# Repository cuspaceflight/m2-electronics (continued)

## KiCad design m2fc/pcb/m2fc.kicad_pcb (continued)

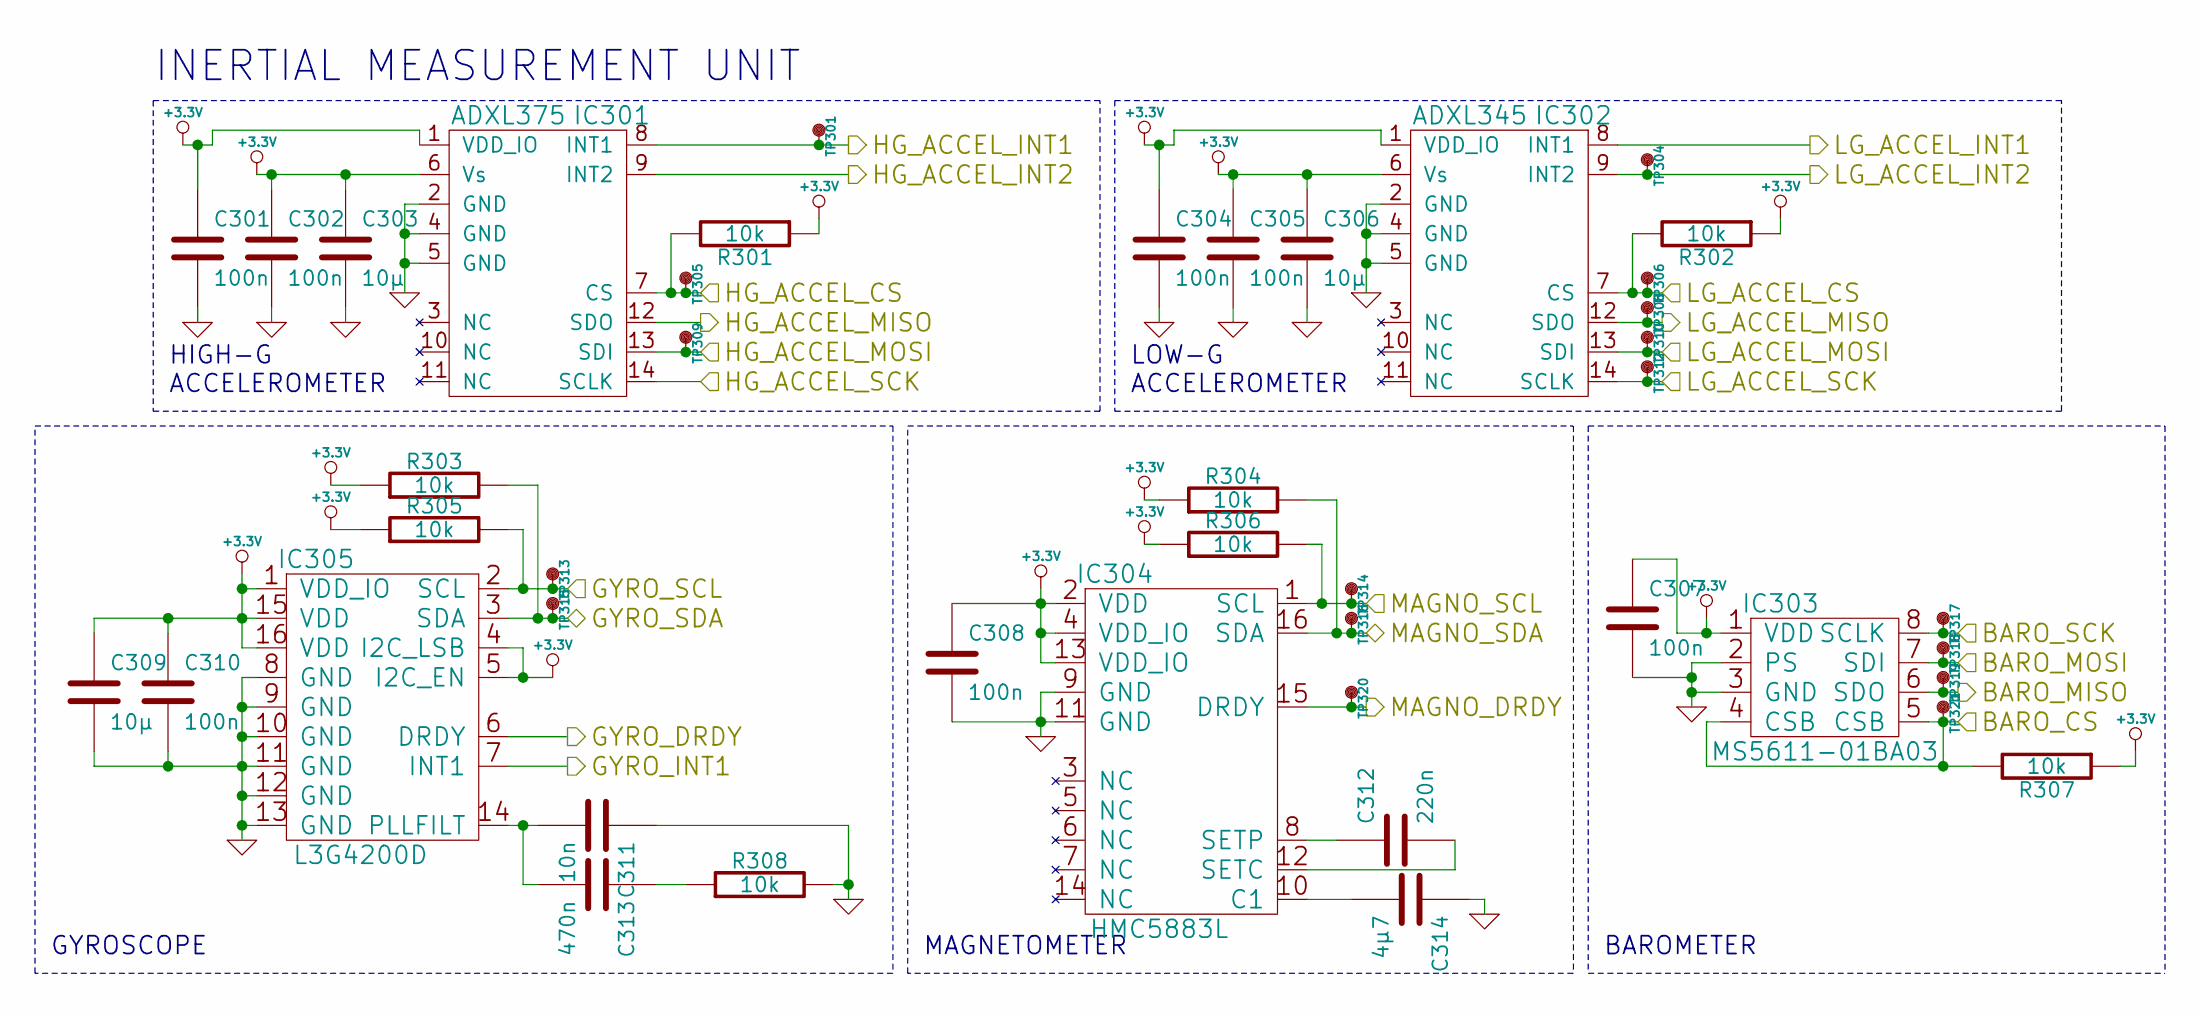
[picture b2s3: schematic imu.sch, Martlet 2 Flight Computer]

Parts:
C301, C302, C304, C305, C307, C308, C310: 100n; C0603; Farnell 1759037
C303, C306, C309: 10µ; C0603; Farnell 2211164
C311: 10n; C0603; Farnell 1833876
C312: 220n; C0603; Farnell 1833865
C313: 470n; C0603; Farnell 1867949
C314: 4µ7; C0603; Farnell 1833803
IC301: ADXL375; ADXL3x5; Farnell 2361527
IC302: ADXL345; ADXL3x5; Farnell 1853935
IC303: MS5611-01BA03; MS5611-01BA; Farnell 2362662
IC304: HMC5883L; Farnell 1971743
IC305: L3G4200D; Farnell 1872924
R301, R302, R303, R304, R305, R306, R307, R308: 10k; R0603; Farnell 2332016
TP301, TP304, TP305, TP306, TP308, TP309, TP310, TP312, TP313, TP314, TP315, TP316, TP317, TP318, TP319, TP320, TP321: TESTPAD

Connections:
+3.3V: C301.1, C302.1, C303.1, C304.1, C305.1, C306.1, C307.1, C308.1, C309.1, C310.1, IC301.1 (VDD_IO), IC301.6 (Vs), IC302.1 (VDD_IO), IC302.6 (Vs), IC303.1 (VDD), IC304.2 (VDD), IC304.4 (VDD_IO), IC304.13 (VDD_IO), IC305.1 (VDD_IO), IC305.4 (I2C_LSB), IC305.5 (I2C_EN), IC305.15 (VDD), IC305.16 (VDD), R301.1, R302.1, R303.1, R304.1, R305.1, R306.1, R307.1; also elsewhere on the board
/IMU/BARO_CS: IC303.4 (CSB), IC303.5 (CSB), R307.2, TP321.1; also elsewhere on the board
/IMU/BARO_MISO: IC303.6 (SDO), TP319.1; also elsewhere on the board
/IMU/BARO_MOSI: IC303.7 (SDI), TP318.1; also elsewhere on the board
/IMU/BARO_SCK: IC303.8 (SCLK), TP317.1; also elsewhere on the board
/IMU/GYRO_DRDY: IC305.6 (DRDY); also elsewhere on the board
/IMU/GYRO_INT1: IC305.7 (INT1); also elsewhere on the board
/IMU/GYRO_SCL: IC305.2 (SCL), R305.2, TP313.1; also elsewhere on the board
/IMU/GYRO_SDA: IC305.3 (SDA), R303.2, TP315.1; also elsewhere on the board
/IMU/HG_ACCEL_CS: IC301.7 (CS), R301.2, TP305.1; also elsewhere on the board
/IMU/HG_ACCEL_INT1: IC301.8 (INT1), TP301.1; also elsewhere on the board
/IMU/HG_ACCEL_INT2: IC301.9 (INT2); also elsewhere on the board
/IMU/HG_ACCEL_MISO: IC301.12 (SDO); also elsewhere on the board
/IMU/HG_ACCEL_MOSI: IC301.13 (SDI), TP309.1; also elsewhere on the board
/IMU/HG_ACCEL_SCK: IC301.14 (SCLK); also elsewhere on the board
/IMU/LG_ACCEL_CS: IC302.7 (CS), R302.2, TP306.1; also elsewhere on the board
/IMU/LG_ACCEL_INT1: IC302.8 (INT1); also elsewhere on the board
/IMU/LG_ACCEL_INT2: IC302.9 (INT2), TP304.1; also elsewhere on the board
/IMU/LG_ACCEL_MISO: IC302.12 (SDO), TP308.1; also elsewhere on the board
/IMU/LG_ACCEL_MOSI: IC302.13 (SDI), TP310.1; also elsewhere on the board
/IMU/LG_ACCEL_SCK: IC302.14 (SCLK), TP312.1; also elsewhere on the board
/IMU/MAGNO_DRDY: IC304.15 (DRDY), TP320.1; also elsewhere on the board
/IMU/MAGNO_SCL: IC304.1 (SCL), R306.2, TP314.1; also elsewhere on the board
/IMU/MAGNO_SDA: IC304.16 (SDA), R304.2, TP316.1; also elsewhere on the board
GND: C301.2, C302.2, C303.2, C304.2, C305.2, C306.2, C307.2, C308.2, C309.2, C310.2, C311.1, C314.1, IC301.2 (GND), IC301.4 (GND), IC301.5 (GND), IC302.2 (GND), IC302.4 (GND), IC302.5 (GND), IC303.2 (PS), IC303.3 (GND), IC304.9 (GND), IC304.11 (GND), IC305.8 (GND), IC305.9 (GND), IC305.10 (GND), IC305.11 (GND), IC305.12 (GND), IC305.13 (GND), R308.2; also elsewhere on the board
unnamed: C311.2, C313.2, IC305.14 (PLLFILT)
unnamed: C312.1, IC304.8 (SETP)
unnamed: C312.2, IC304.12 (SETC)
unnamed: C313.1, R308.1
unnamed: C314.2, IC304.10 (C1)

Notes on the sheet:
HIGH-G ACCELEROMETER
LOW-G ACCELEROMETER
GYROSCOPE
MAGNETOMETER
BAROMETER
INERTIAL MEASUREMENT UNIT

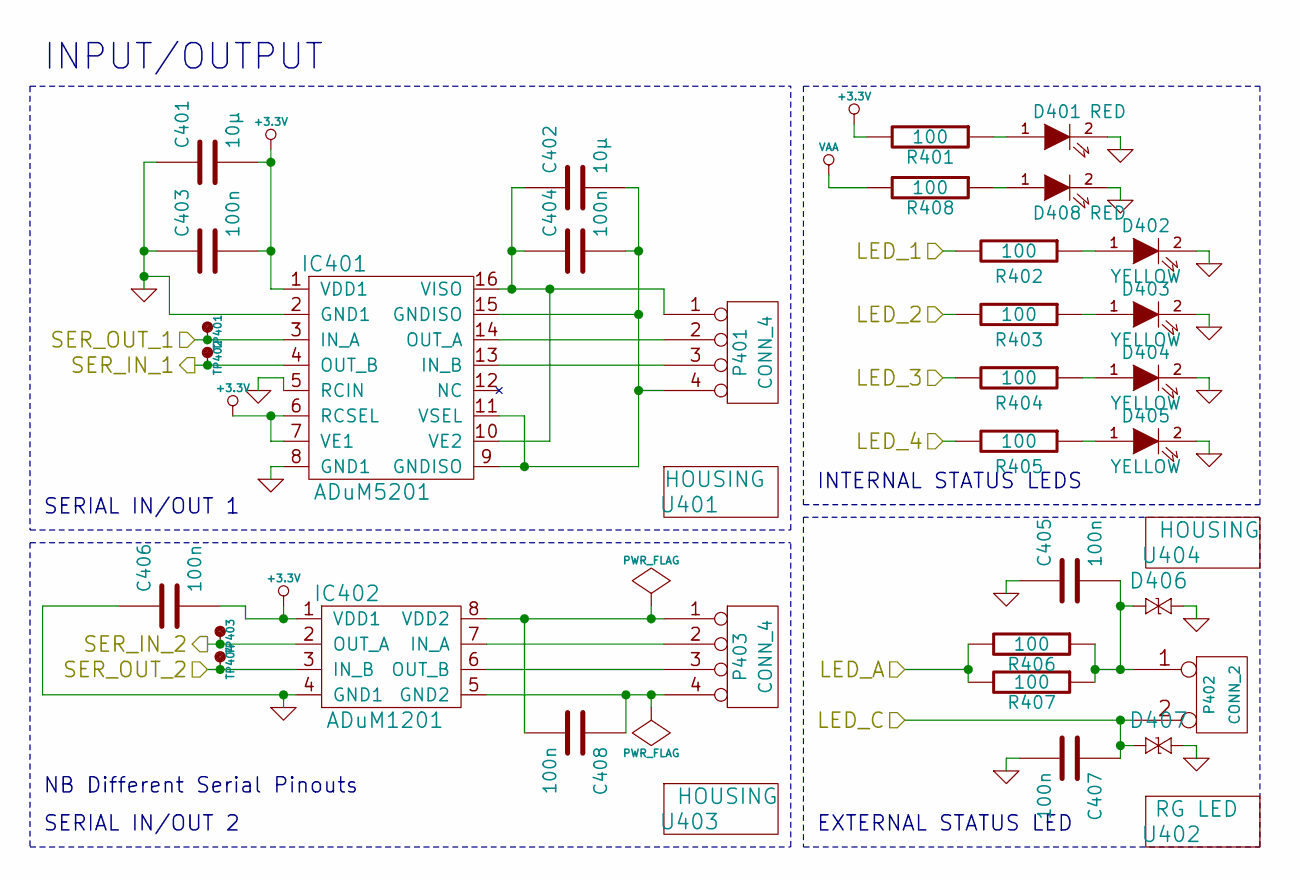
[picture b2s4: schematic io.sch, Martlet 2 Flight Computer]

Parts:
C401, C402: 10µ; C0603; Farnell 2211164
C403, C404, C405, C406, C407, C408: 100n; C0603; Farnell 1759037
D401, D408: RED; LED0603; Farnell 2290329
D402, D403, D404, D405: YELLOW; LED0603; Farnell 2290330
D406, D407: CGA0402MLC-12G; R0402; Farnell 2368169
IC401: ADuM5201; SOIC16; Farnell 2067773
IC402: ADuM1201; SOIC8; Farnell 1078200
P401, P403: CONN_4; S04B-PASK-2; Farnell 1830749
P402: CONN_2; S02B-PASK-2; Farnell 1830747
R401, R402, R403, R404, R405, R406, R407, R408: 100; R0603; Farnell 2331989
TP401, TP402, TP403, TP404: TESTPAD
U401, U403: HOUSING; Farnell 1830729
U402: RG LED; Farnell 1142488
U404: HOUSING; Farnell 1830726

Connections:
+3.3V: C401.2, C403.2, C406.2, IC401.1 (VDD1), IC401.6 (RCSEL), IC401.7 (VE1), IC402.1 (VDD1), R401.2; also elsewhere on the board
/IO/LED_1: R402.2; also elsewhere on the board
/IO/LED_2: R403.2; also elsewhere on the board
/IO/LED_3: R404.2; also elsewhere on the board
/IO/LED_4: R405.2; also elsewhere on the board
/IO/LED_A: R406.2, R407.2; also elsewhere on the board
/IO/LED_C: C407.1, D407.2, P402.2 (PM); also elsewhere on the board
/IO/SER_IN_1: IC401.4 (OUT_B), TP402.1; also elsewhere on the board
/IO/SER_IN_2: IC402.2 (OUT_A), TP403.1; also elsewhere on the board
/IO/SER_OUT_1: IC401.3 (IN_A), TP401.1; also elsewhere on the board
/IO/SER_OUT_2: IC402.3 (IN_B), TP404.1; also elsewhere on the board
GND: C401.1, C403.1, C405.1, C406.1, C407.2, D401.2 (K), D402.2 (K), D403.2 (K), D404.2 (K), D405.2 (K), D406.1, D407.1, D408.2 (K), IC401.2 (GND1), IC401.5 (RCIN), IC401.8 (GND1), IC402.4 (GND1); also elsewhere on the board
unnamed: C402.1, C404.1, IC401.10 (VE2), IC401.16 (VISO), P401.1
unnamed: C402.2, C404.2, IC401.9 (GNDISO), IC401.11 (VSEL), IC401.15 (GNDISO), P401.4
unnamed: C405.2, D406.2, P402.1, R406.1, R407.1
unnamed: C408.1, IC402.5 (GND2), P403.4
unnamed: C408.2, IC402.8 (VDD2), P403.1
unnamed: D401.1 (A), R401.1
unnamed: D402.1 (A), R402.1
unnamed: D403.1 (A), R403.1
unnamed: D404.1 (A), R404.1
unnamed: D405.1 (A), R405.1
unnamed: D408.1 (A), R408.1
unnamed: IC401.13 (IN_B), P401.3
unnamed: IC401.14 (OUT_A), P401.2
unnamed: IC402.6 (OUT_B), P403.3
unnamed: IC402.7 (IN_A), P403.2
VAA: R408.2; also elsewhere on the board

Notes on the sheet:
SERIAL IN/OUT 1
EXTERNAL STATUS LED
INTERNAL STATUS LEDS
INPUT/OUTPUT
SERIAL IN/OUT 2
NB Different Serial Pinouts

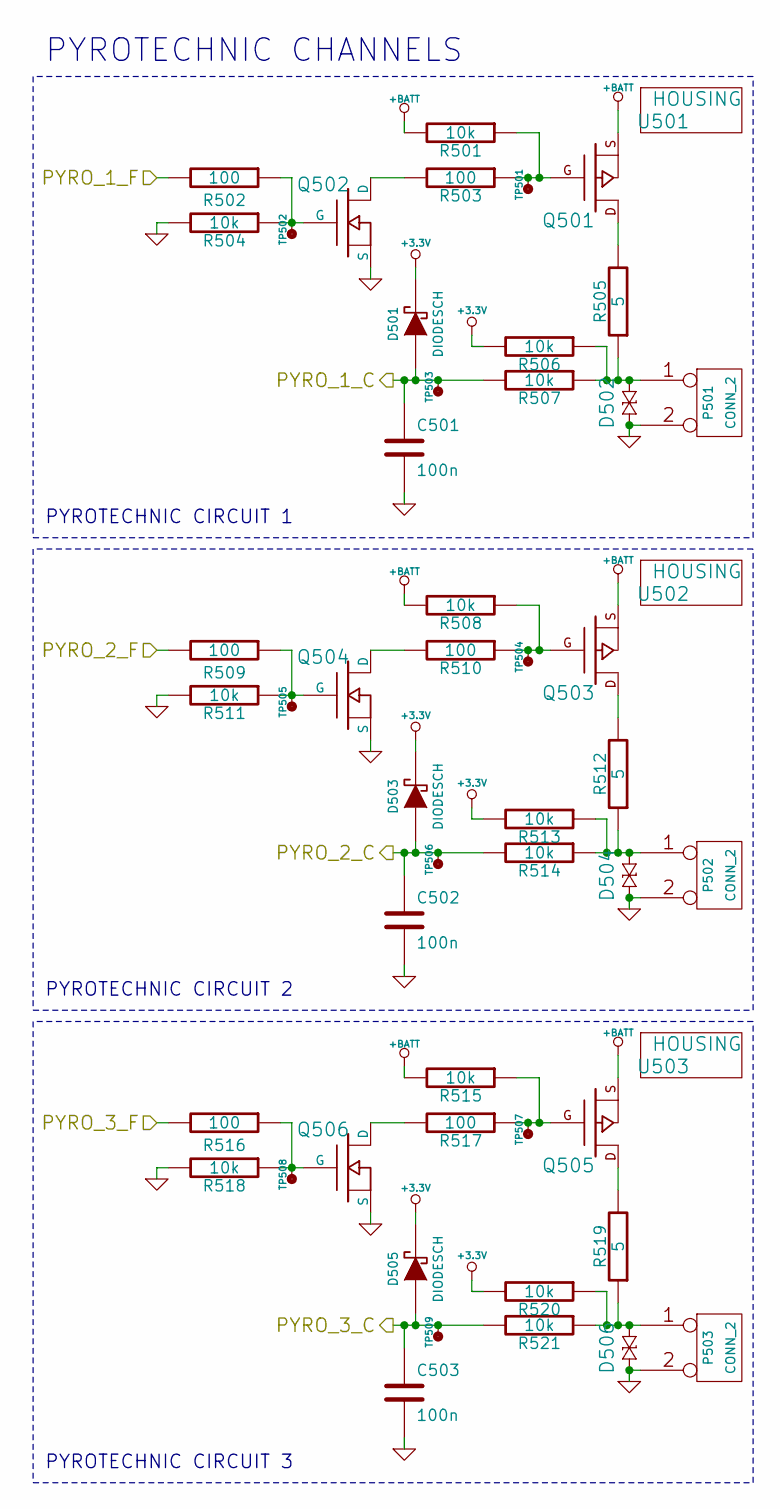
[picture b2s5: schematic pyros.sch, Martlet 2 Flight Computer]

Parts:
C501, C502, C503: 100n; C0603; Farnell 1759037
D501, D503, D505: DIODESCH; SOD323; Farnell 1349646
D502, D504, D506: CGA0402MLC-12G; R0402; Farnell 2368169
P501, P502, P503: CONN_2; S02B-PASK-2; Farnell 1830747
Q501, Q503, Q505: MOSFET_P; SOT-23-MOSFET; Farnell 1894738
Q502, Q504, Q506: MOSFET_N; SOT-23-MOSFET; Farnell 1510761
R501, R504, R506, R507, R508, R511, R513, R514, R515, R518, R520, R521: 10k; R0603; Farnell 2332016
R502, R503, R509, R510, R516, R517: 100; R0603; Farnell 2331989
R505, R512, R519: 5; PWR4318; Farnell 2328356
TP501, TP502, TP503, TP504, TP505, TP506, TP507, TP508, TP509: TESTPAD
U501, U502, U503: HOUSING; Farnell 1830726

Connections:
+3.3V: D501.2 (K), D503.2 (K), D505.2 (K), R506.2, R513.2, R520.2; also elsewhere on the board
+BATT: Q501.S, Q503.S, Q505.S, R501.2, R508.2, R515.2; also elsewhere on the board
/Pyros/PYRO_1_C: C501.1, D501.1 (A), R507.2, TP503.1; also elsewhere on the board
/Pyros/PYRO_1_F: R502.2; also elsewhere on the board
/Pyros/PYRO_2_C: C502.1, D503.1 (A), R514.2, TP506.1; also elsewhere on the board
/Pyros/PYRO_2_F: R509.2; also elsewhere on the board
/Pyros/PYRO_3_C: C503.1, D505.1 (A), R521.2, TP509.1; also elsewhere on the board
/Pyros/PYRO_3_F: R516.2; also elsewhere on the board
GND: C501.2, C502.2, C503.2, D502.2, D504.2, D506.2, P501.2 (PM), P502.2 (PM), P503.2 (PM), Q502.S, Q504.S, Q506.S, R504.2, R511.2, R518.2; also elsewhere on the board
unnamed: D502.1, P501.1, R505.1, R506.1, R507.1
unnamed: D504.1, P502.1, R512.1, R513.1, R514.1
unnamed: D506.1, P503.1, R519.1, R520.1, R521.1
unnamed: Q501.D, R505.2
unnamed: Q501.G, R501.1, R503.1, TP501.1
unnamed: Q502.D, R503.2
unnamed: Q502.G, R502.1, R504.1, TP502.1
unnamed: Q503.D, R512.2
unnamed: Q503.G, R508.1, R510.1, TP504.1
unnamed: Q504.D, R510.2
unnamed: Q504.G, R509.1, R511.1, TP505.1
unnamed: Q505.D, R519.2
unnamed: Q505.G, R515.1, R517.1, TP507.1
unnamed: Q506.D, R517.2
unnamed: Q506.G, R516.1, R518.1, TP508.1

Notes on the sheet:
PYROTECHNIC CIRCUIT 1
PYROTECHNIC CHANNELS
PYROTECHNIC CIRCUIT 2
PYROTECHNIC CIRCUIT 3

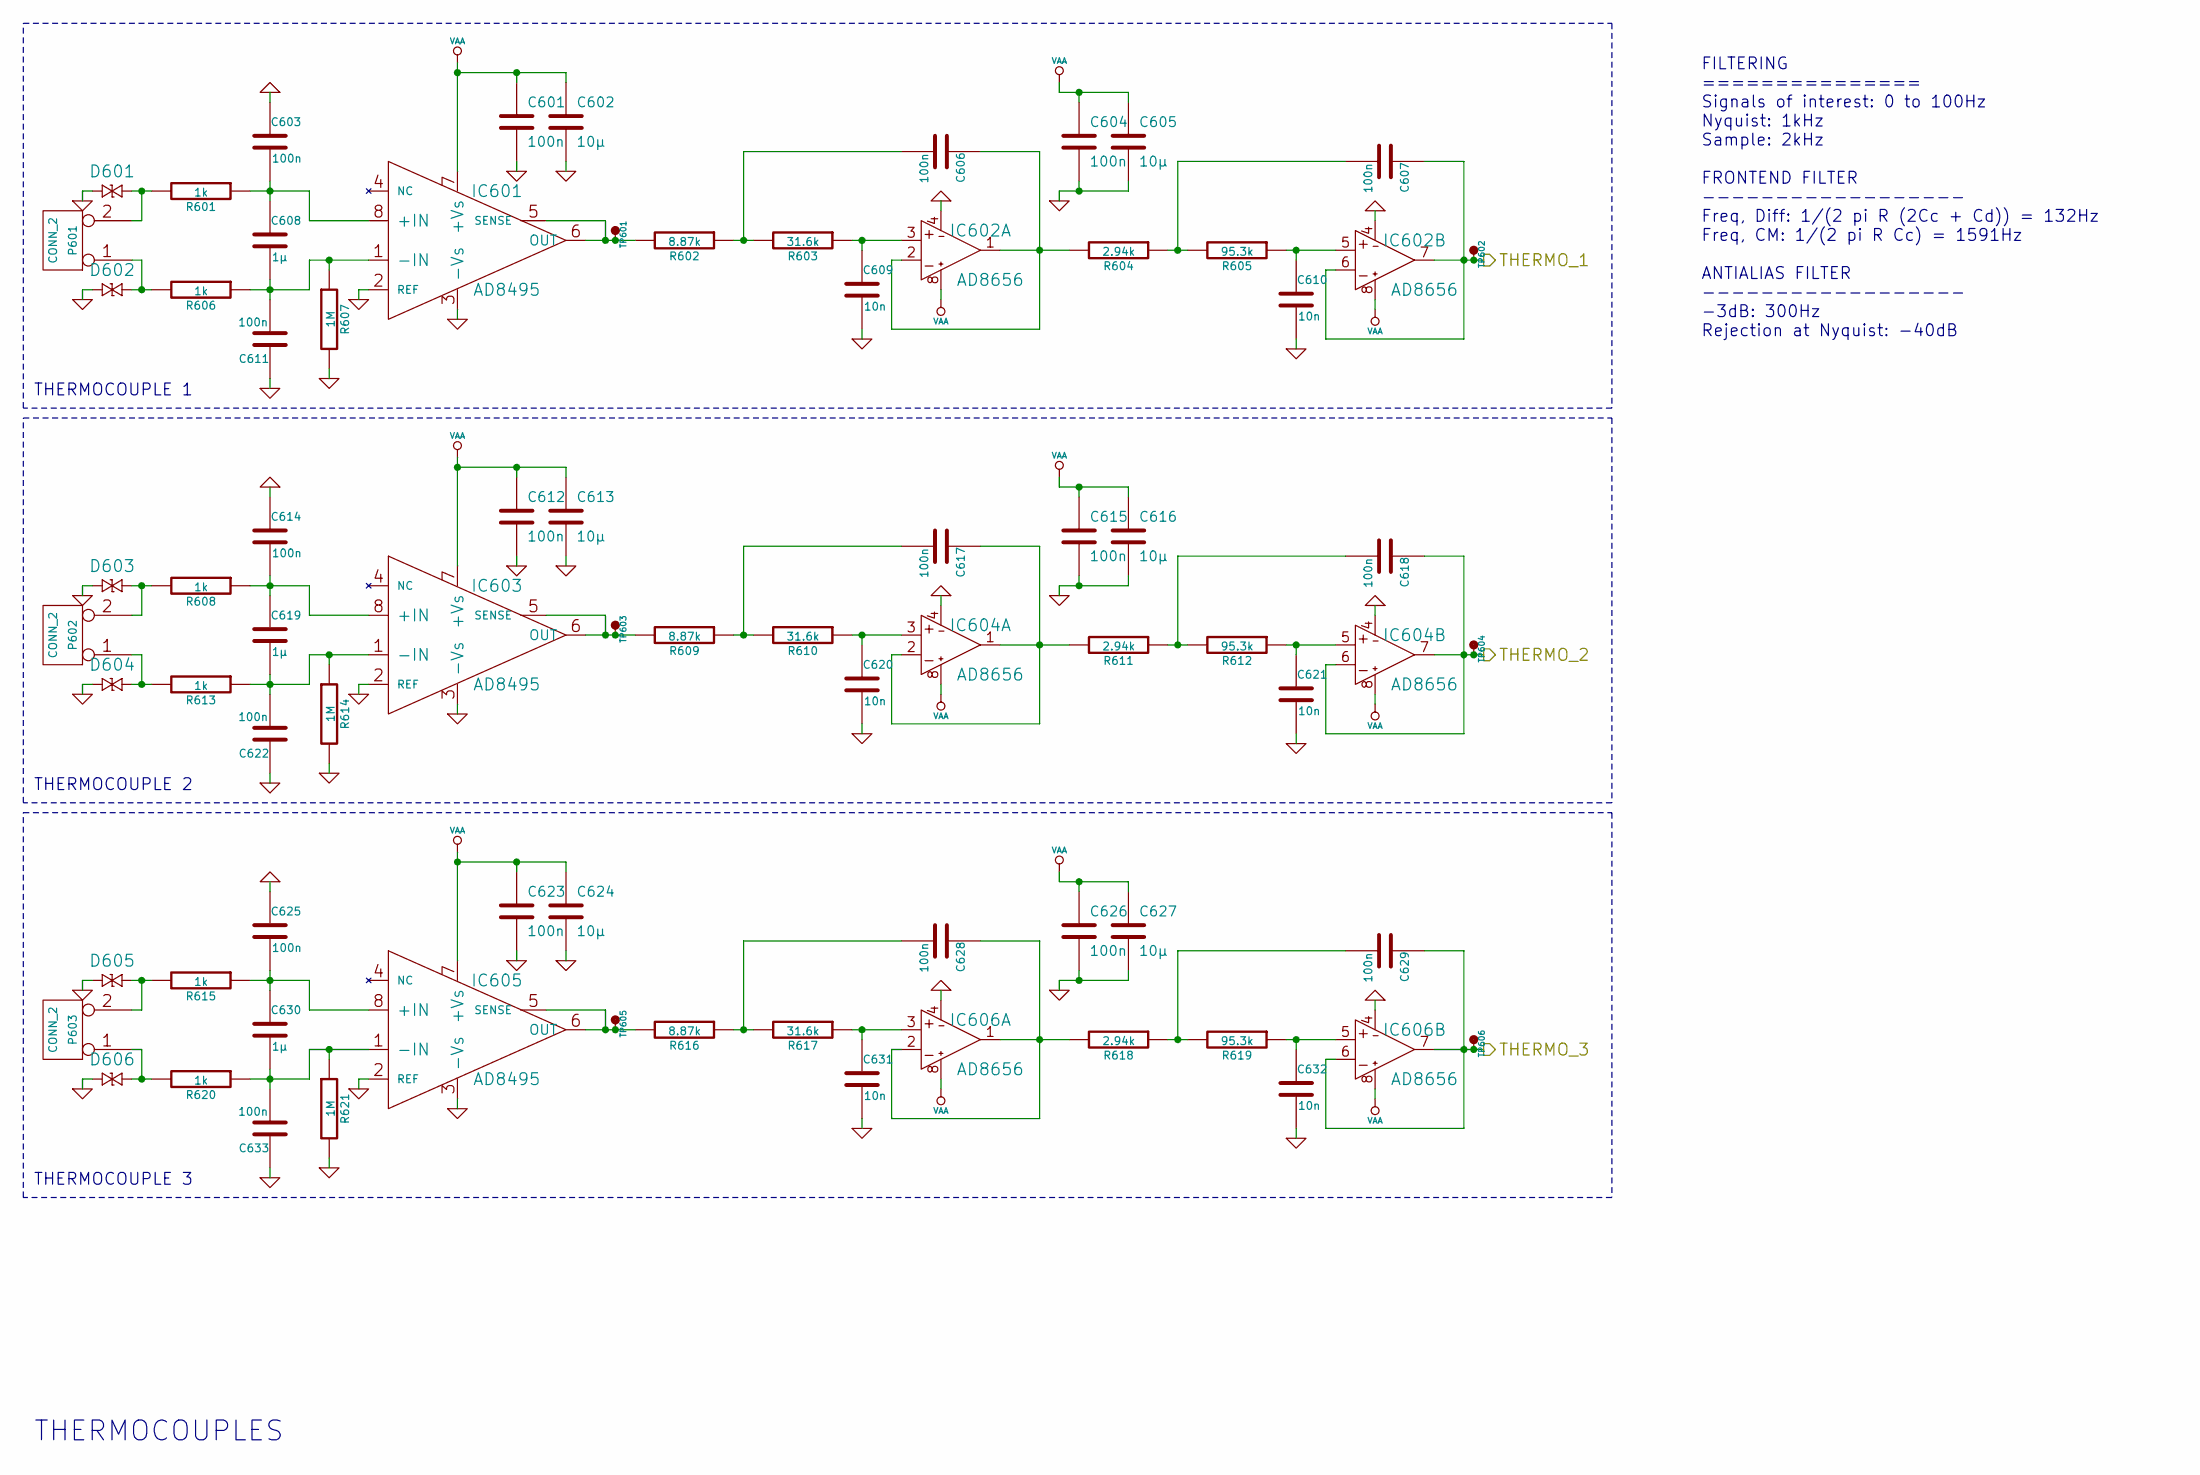
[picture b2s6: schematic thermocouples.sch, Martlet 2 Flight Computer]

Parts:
C601, C604, C612, C615, C623, C626: 100n; C0603; Farnell 1759037
C602, C605, C613, C616, C624, C627: 10µ; C0603; Farnell 2211164
C603, C606, C607, C611, C614, C617, C618, C622, C625, C628, C629, C633: 100n; C1206; Farnell 2211074
C608, C619, C630: 1µ; C0603; Farnell 2346895
C609, C610, C620, C621, C631, C632: 10n; C0603; Farnell 2112704
D601, D602, D603, D604, D605, D606: CGA0402MLC-12G; R0402; Farnell 2368169
IC601, IC603, IC605: AD8495; MSOP8; Farnell 2067807
IC602, IC604, IC606: AD8656; MSOP8; Farnell 1858055
P601, P602, P603: CONN_2; S02B-PASK-2; Farnell 1830747
R601, R606, R608, R613, R615, R620: 1k; R0603; Farnell 2116678
R602, R609, R616: 8.87k; R0603; Farnell 2116779
R603, R610, R617: 31.6k; R0603; Farnell 2116838
R604, R611, R618: 2.94k; R0603; Farnell 2116727
R605, R612, R619: 95.3k; R0603; Farnell 2116889
R607, R614, R621: 1M; R0603; Farnell 2321755
TP601, TP602, TP603, TP604, TP605, TP606: TESTPAD

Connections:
/Thermocouples/THERMO_1: C607.1, IC602.6 (-IN), IC602.7 (OUT), TP602.1; also elsewhere on the board
/Thermocouples/THERMO_2: C618.1, IC604.6 (-IN), IC604.7 (OUT), TP604.1; also elsewhere on the board
/Thermocouples/THERMO_3: C629.1, IC606.6 (-IN), IC606.7 (OUT), TP606.1; also elsewhere on the board
GND: C601.2, C602.2, C603.1, C604.2, C605.2, C609.2, C610.2, C611.1, C612.2, C613.2, C614.1, C615.2, C616.2, C620.2, C621.2, C622.1, C623.2, C624.2, C625.1, C626.2, C627.2, C631.2, C632.2, C633.1, D601.2, D602.2, D603.2, D604.2, D605.2, D606.2, IC601.2 (REF), IC601.3 (-Vs), IC602.4 (V-), IC603.2 (REF), IC603.3 (-Vs), IC604.4 (V-), IC605.2 (REF), IC605.3 (-Vs), IC606.4 (V-), R607.2, R614.2, R621.2; also elsewhere on the board
unnamed: C603.2, C608.1, IC601.8 (+IN), R601.1
unnamed: C606.1, IC602.1 (OUT), IC602.2 (-IN), R604.2
unnamed: C606.2, R602.1, R603.2
unnamed: C607.2, R604.1, R605.2
unnamed: C608.2, C611.2, IC601.1 (-IN), R606.1, R607.1
unnamed: C609.1, IC602.3 (+IN), R603.1
unnamed: C610.1, IC602.5 (+IN), R605.1
unnamed: C614.2, C619.1, IC603.8 (+IN), R608.1
unnamed: C617.1, IC604.1 (OUT), IC604.2 (-IN), R611.2
unnamed: C617.2, R609.1, R610.2
unnamed: C618.2, R611.1, R612.2
unnamed: C619.2, C622.2, IC603.1 (-IN), R613.1, R614.1
unnamed: C620.1, IC604.3 (+IN), R610.1
unnamed: C621.1, IC604.5 (+IN), R612.1
unnamed: C625.2, C630.1, IC605.8 (+IN), R615.1
unnamed: C628.1, IC606.1 (OUT), IC606.2 (-IN), R618.2
unnamed: C628.2, R616.1, R617.2
unnamed: C629.2, R618.1, R619.2
unnamed: C630.2, C633.2, IC605.1 (-IN), R620.1, R621.1
unnamed: C631.1, IC606.3 (+IN), R617.1
unnamed: C632.1, IC606.5 (+IN), R619.1
unnamed: D601.1, P601.2 (PM), R601.2
unnamed: D602.1, P601.1, R606.2
unnamed: D603.1, P602.2 (PM), R608.2
unnamed: D604.1, P602.1, R613.2
unnamed: D605.1, P603.2 (PM), R615.2
unnamed: D606.1, P603.1, R620.2
unnamed: IC601.5 (SENSE), IC601.6 (OUT), R602.2, TP601.1
unnamed: IC603.5 (SENSE), IC603.6 (OUT), R609.2, TP603.1
unnamed: IC605.5 (SENSE), IC605.6 (OUT), R616.2, TP605.1
VAA: C601.1, C602.1, C604.1, C605.1, C612.1, C613.1, C615.1, C616.1, C623.1, C624.1, C626.1, C627.1, IC601.7 (+Vs), IC602.8 (V+), IC603.7 (+Vs), IC604.8 (V+), IC605.7 (+Vs), IC606.8 (V+); also elsewhere on the board

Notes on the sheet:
FILTERING =============== Signals of interest: 0 to 100Hz Nyquist: 1kHz Sample: 2kHz FRONTEND FILTER ------------------ Freq, Diff: 1/(2 pi R (2Cc + Cd)) = 132Hz Freq, CM: 1/(2 pi R Cc) = 1591Hz ANTIALIAS FILTER ------------------ -3dB: 300Hz Rejection at Nyquist: -40dB
THERMOCOUPLES
THERMOCOUPLE 1
THERMOCOUPLE 2
THERMOCOUPLE 3

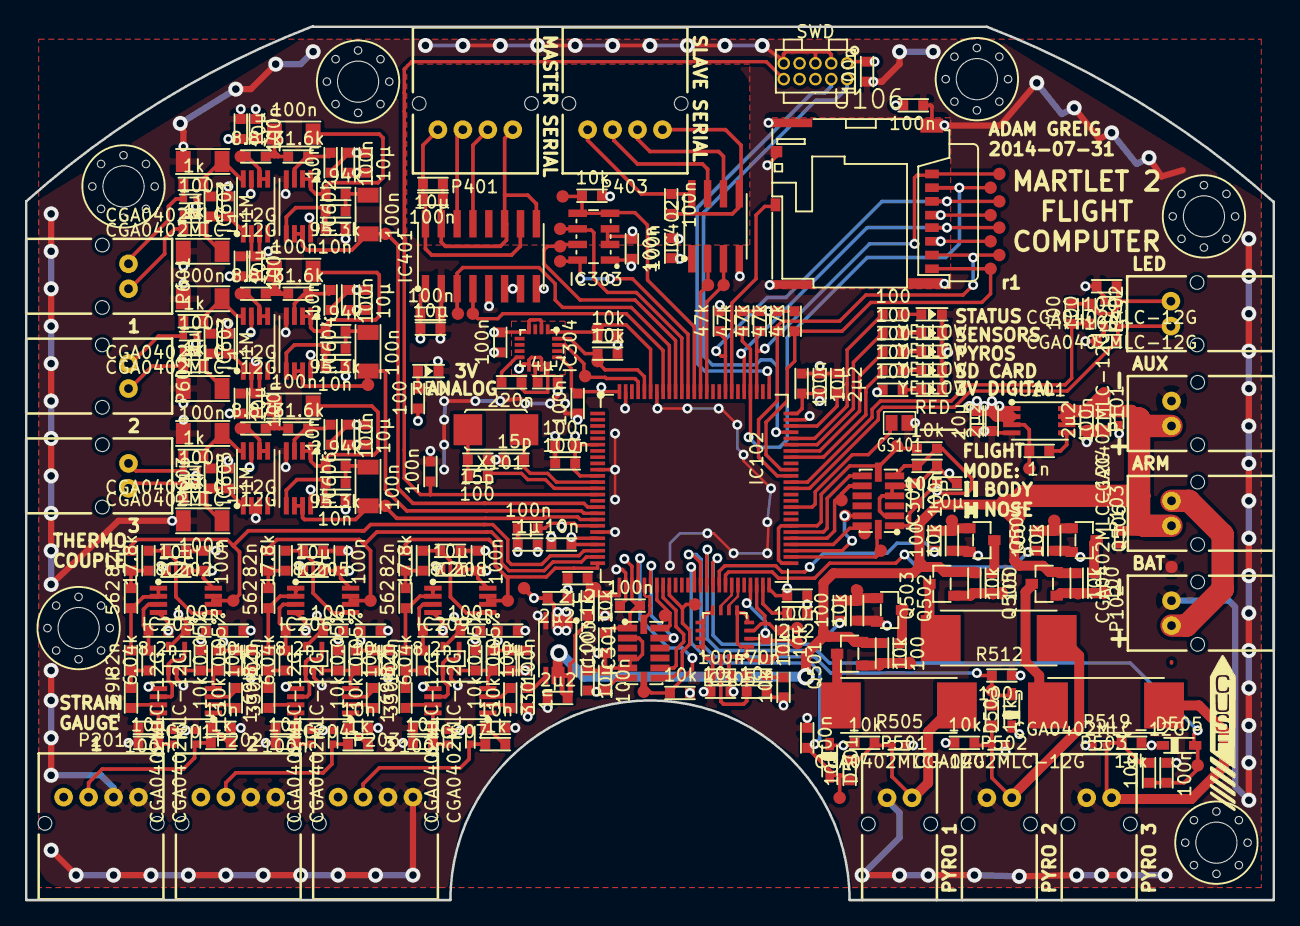
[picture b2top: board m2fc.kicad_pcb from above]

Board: 4 copper layers, 100.0 x 70.0 mm, 351 parts (1 on the bottom side), 170 nets.

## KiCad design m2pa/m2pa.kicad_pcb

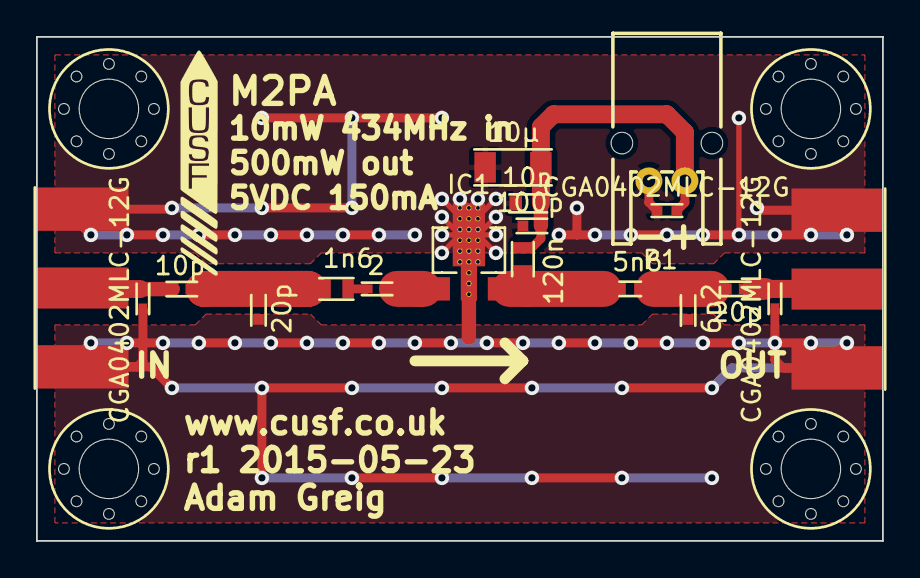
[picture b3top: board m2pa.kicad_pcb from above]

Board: 2 copper layers, 47.0 x 28.0 mm, 22 parts (0 on the bottom side), 9 nets.

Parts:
C1: 10p; C0402
C2, C7: 20p; C0402
C3: 100p; C0402
C4: 10n; C0603
C5: 6p2; C0402
C6: 10µ; C1206
D1, D2, D3: CGA0402MLC-12G; R0402
IC1: ADL5324; SOT89-3
L1: 1n6; L0603
L2: 120n; L0603
L3: 5n6; L0402
M3_MOUNT, M3_MOUNT#2, M3_MOUNT#3, M3_MOUNT#4: VAL**; M3_MOUNT
P1: CONN_01X02; S02B-PASK-2
P2, P3: SMA; SMA-142-0701-801
R1: 2; R0402

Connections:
+5V: C3.1, C4.1, C6.1, D3.1, L2.2, P1.2
GND: C2.1, C3.2, C4.2, C5.1, C6.2, D1.2, D2.2, D3.2, IC1.2, P1.1, P2.2, P2.3, P2.4, P2.5, P3.2, P3.3, P3.4, P3.5
unnamed: C1.1, C2.2, L1.2
unnamed: C1.2, D1.1, P2.1
unnamed: C5.2, C7.1, L3.1
unnamed: C7.2, D2.1, P3.1
unnamed: IC1.1, R1.1
unnamed: IC1.3, L2.1, L3.2
unnamed: L1.1, R1.2

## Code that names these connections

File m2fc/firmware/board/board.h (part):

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/*
 * GPIOA setup:
 *
 * PA0  - STRAIN_1                  (analogue input).
 * PA1  - STRAIN_2                  (analogue input).
 * PA2  - STRAIN_3                  (analogue input).
 * PA3  - BAT_MON                   (analogue input).
 * PA4  - HG_ACCEL_CS               (output pushpull).
 * PA5  - HG_ACCEL_SCK              (alternate 5).
 * PA6  - HG_ACCEL_MISO             (alternate 5).
 * PA7  - HG_ACCEL_MOSI             (alternate 5).
 * PA8  - PIN8                      (input pullup).
 * PA9  - LED_SDCARD                (output pushpull).
 * PA10 - LED_PYROS                 (output pushpull).
 * PA11 - LED_SENSORS               (output pushpull).
 * PA12 - LED_STATUS                (output pushpull).
 * PA13 - SWDIO                     (alternate 0).
 * PA14 - SWCLK                     (alternate 0).
 * PA15 - PIN15                     (input pullup).
 */
#define VAL_GPIOA_MODER             (PIN_MODE_ANALOG(GPIOA_STRAIN_1)        |\
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 * GPIOB setup:
 *
 * PB0  - PIN0                      (input pullup).
 * PB1  - PIN1                      (input pullup).
 * PB2  - PIN2                      (input pullup).
 * PB3  - BARO_SCK                  (alternate 6).
 * PB4  - BARO_MISO                 (alternate 6).
 * PB5  - BARO_MOSI                 (alternate 6).
 * PB6  - SER_OUT_1                 (alternate 7).
 * PB7  - SER_IN_1                  (alternate 7).
 * PB8  - MAGNO_SCL                 (alternate 4).
 * PB9  - MAGNO_SDA                 (alternate 4).
 * PB10 - GYRO_SCL                  (alternate 4).
 * PB11 - GYRO_SDA                  (alternate 4).
 * PB12 - LG_ACCEL_CS               (output pushpull).
 * PB13 - LG_ACCEL_SCK              (alternate 5).
 * PB14 - LG_ACCEL_MISO             (alternate 5).
 * PB15 - LG_ACCEL_MOSI             (alternate 5).
 */
#define VAL_GPIOB_MODER             (PIN_MODE_INPUT(GPIOB_PIN0)             |\
                                     PIN_MODE_INPUT(GPIOB_PIN1)             |\
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 * GPIOC setup:
 *
 * PC0  - PIN0                      (input pullup).
 * PC1  - THERMO_1                  (analogue input).
 * PC2  - THERMO_2                  (analogue input).
 * PC3  - THERMO_3                  (analogue input).
 * PC4  - HG_ACCEL_INT2             (input pullup).
 * PC5  - HG_ACCEL_INT1             (input pullup).
 * PC6  - LED_C                     (output pushpull).
 * PC7  - LED_A                     (output pushpull).
 * PC8  - SD_DAT0                   (alternate 12).
 * PC9  - SD_DAT1                   (alternate 12).
 * PC10 - SD_DAT2                   (alternate 12).
 * PC11 - SD_DAT3                   (alternate 12).
 * PC12 - SD_CLK                    (alternate 12).
 * PC13 - PIN13                     (input pullup).
 * PC14 - PIN14                     (input pullup).
 * PC15 - PIN15                     (input pullup).
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 * GPIOD setup:
 *
 * PD0  - PIN0                      (input pullup).
 * PD1  - SD_CD                     (input pullup).
 * PD2  - SD_CMD                    (alternate 12).
 * PD3  - PIN3                      (input pullup).
 * PD4  - PIN4                      (input pullup).
 * PD5  - SER_OUT_2                 (alternate 7).
 * PD6  - SER_IN_2                  (alternate 7).
 * PD7  - BARO_CS                   (output pushpull).
 * PD8  - LG_ACCEL_INT2             (input pullup).
 * PD9  - LG_ACCEL_INT1             (input pullup).
 * PD10 - LG_ACCEL_CS               (input pullup, pin driven by PB12).
 * PD11 - PIN11                     (input pullup).
 * PD12 - PIN12                     (input pullup).
 * PD13 - SJ1                       (input pullup).
 * PD14 - PIN14                     (input pullup).
 * PD15 - PIN15                     (input pullup).
 */
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/*
 * GPIOE setup:
 *
 * PE0  - MAGNO_DRDY                (input pullup).
 * PE1  - PIN1                      (input pullup).
 * PE2  - PIN2                      (input pullup).
 * PE3  - PIN3                      (input pullup).
 * PE4  - PIN4                      (input pullup).
 * PE5  - PIN5                      (input pullup).
 * PE6  - PIN6                      (input pullup).
 * PE7  - PYRO_1_C                  (input pullup).
 * PE8  - PYRO_2_C                  (input pullup).
 * PE9  - PYRO_3_C                  (input pullup).
 * PE10 - PYRO_1_F                  (output pushpull).
 * PE11 - PYRO_2_F                  (output pushpull).
 * PE12 - PYRO_3_F                  (output pushpull).
 * PE13 - GYRO_INT1                 (input pullup).
 * PE14 - GYRO_DRDY                 (input pullup).
 * PE15 - PIN15                     (input pullup).
 */
#define VAL_GPIOE_MODER             (PIN_MODE_INPUT(GPIOE_MAGNO_DRDY)       |\
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
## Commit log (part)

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2014-04-30 Initial commit.
2014-05-06 first go at schematic
2014-05-08 m2p sch looking good
2014-05-08 reorganise repo a little
2014-05-08 reorganise some more
2014-05-08 add README
2014-05-08 can't spell
2014-05-08 add battery voltage monitoring
2014-05-09 swap to an STM32 chip
2014-05-09 annotate parts
2014-05-09 fix a few typos
2014-05-09 rearrange LEDs a little
2014-05-09 new BOM
2014-05-09 respec parts for stock level
2014-05-09 stm32 is lqfp package
2014-05-09 add power flags so ERC all pass
2014-05-09 add part number for ic2
2014-05-09 put LED on JNTRST instead of continuity measure
2014-05-19 place most major parts for m2r
2014-05-20 add first go at m2r schematic
2014-05-20 add PDF out of m2r
2014-05-20 spec crystal part
2014-05-20 swap STM32F103 for STM32F303
2014-05-22 finish up m2r schematic
2014-05-22 use two 100R to make up 50R because lol
2014-05-22 swap 50R to two 100R on m2p too
2014-05-22 oops, annotate
2014-05-27 Add second connector for arming switch to m2r
2014-05-27 add separate connector for arming switch to m2p
2014-05-27 Change F103 to F303 on m2p
2014-05-29 swap SP100-2T for MS5611-01BA03 barometer
2014-05-29 add farnell number for new barometer
2014-05-29 update farnell codes
2014-05-30 add most of the libraries m2d'l probs want
2014-06-19 make a good start on m2d schematic
2014-07-02 swap to f415, reorg sch into sheets, spec strain gauge Rg
2014-07-05 rename m2d to m2fc which now incorporates m2p
2014-07-09 update more bits on flight computer..
2014-07-10 everything... wired... up...
2014-07-10 fix all the erc errors
2014-07-10 add missing farnell numbers
2014-07-10 add bom
2014-07-10 further wibbling about things
2014-07-10 new PDFs
2014-07-10 something went weird with mtx2 footprint, redo
2014-07-18 update m2fc sch with 3rd pyro and SJs
2014-07-18 new pdf
2014-07-18 reannotate m2r
2014-07-20 swap to JST PA range connectors
2014-07-21 rejig m2r schematic a little for i2c gps
2014-07-22 make all the footprints (and check them twice)
2014-07-22 a good looking ratsnest
2014-07-22 pdf of rearranged pinouts
2014-07-22 m3 footprint
2014-07-22 further pcb work i guess
2014-07-23 2 airwires to go
2014-07-23 0 airwires!
2014-07-23 gps top gnd plane
2014-07-23 pretty silk
2014-07-23 gerbers etc
2014-07-23 jog logo slightly
2014-07-23 no paste on sjs, tps, ants
2014-07-23 shipping
2014-07-23 changed ESD diode to 12V one
2014-07-23 regen gerber zip
2014-07-23 further tweaks
2014-07-23 more gerbers?
2014-07-23 done pls
2014-07-24 quick go at wiring diagram
2014-07-24 ugh ugh
2014-07-24 errata got fixed before production yay
2014-07-24 change alm silk, bottom mask on sma, add better gnd track to rb
2014-07-24 sd pullups, shielded sgs
2014-07-28 add esd diodes to m2fc
2014-07-28 add PDFs of filter specs
2014-07-30 m2fc footprints, start layout
2014-07-30 layout going ok so far...
2014-07-30 about to do something dangerous to pcb
2014-07-30 paid off woo
2014-07-30 omg layout done
2014-07-30 analogue section routed woop woop
2014-07-30 routing continues
2014-07-31 routing intensifies
2014-07-31 nc 0
2014-07-31 tidied up
2014-07-31 more tidying
2014-07-31 flip around power connectors
2014-07-31 done?
2014-07-31 3V ANALOG LED
2014-07-31 update m2fc bom
2014-07-31 ready to go go go
2014-08-01 final checks, tweaks, etc
2014-08-01 shipped
2014-08-01 oh actually regen inner copper 2 and reship
2014-08-06 spec alt part for m2r 10p capacitor
2014-08-06 solder stencil
2014-08-17 add m2pogo board
2014-08-17 change sd card part number on m2fc
2014-08-17 move things out of top level
2014-08-17 add chibiOS submodule
2014-08-17 Set ChibiOS to stable_2.6.x
2014-08-17 set up template for m2fc chibios
2014-08-18 add board definition files
2014-08-18 define all m2fc pins in board.h
2014-08-18 regen m2fc sch
2014-08-18 strip main.c
2014-08-18 blink status LED yay
2014-08-19 working barometer yesss
2014-08-20 tidy ms5611 driver
2014-08-20 add adxl3x5 driver
2014-08-20 add pyro driver
2014-08-20 warn about doubles happening
2014-08-20 basic working microSD example
2014-08-20 WIP on datalogging
2014-08-20 logging to µsd basically working! (modulu speed)
2014-08-20 scatter 'volatile' until everything is AMAZING
2014-09-06 first go at kalman filtering
2014-09-06 changes til it compiles
2014-09-07 altitude from pressure
2014-09-07 further se bits
2014-09-07 add basic mission stuff
2014-09-08 update log analysis
2014-09-08 add times to analyse.py
2014-09-08 fix up time_utils
2014-09-09 add drawings for jack and further m2fc fw bist
2014-09-10 progress
2014-09-12 first go at m2r firmware
2014-09-13 offline kalman filter test
2014-09-13 update state estimation R vals
2014-09-14 change telem format, and everything else
2014-09-14 simplify accel axis; config for m2fc; new plot_flight script
2014-09-16 lay out groundwork for m2r
2014-09-16 work on ublox parsing
2014-09-16 ublox state machine
2014-09-16 brief warning/error func
2014-09-18 gps basically working
2014-09-19 further radio/gps work
2014-09-19 RockBLOCK simple dispatcher implemented, not tested!
2014-09-20 Ignore some stuff
2014-09-20 Initial import of audio data
2014-09-20 Add 'zero' to audio samples.
2014-09-20 Add function to say an altitude using audio samples.
2014-09-20 m2r radio tx bits
2014-09-20 change pyros to 10ms pulses
2014-09-20 fm radio bits
2014-09-20 radio kinda works
2014-09-20 alternate voice and telem
2014-09-20 update main deploy alt
2014-09-20 Added support for M2R <-> M2FC comms using SBP. Sending state set from M2FC.
2014-09-20 rockblock
2014-09-21 have to scrub :( :(
2015-02-26 import AR's new i2c drivers, start bug fixing
2015-03-03 debugged drivers
2015-03-12 magno working
2015-03-13 gyros working
2015-04-15 hey, onboard fm radio working
2015-05-20 add m2r r2 schematic
2015-05-20 remove unused libraries from m2r-r2 sch
2015-05-20 remove old m2r pcb
2015-05-21 almost all m2r r2 routed except vcc lol
2015-05-23 update xml2farnell script for short line notes
2015-05-24 routing updates
2015-05-24 add m2pa
2015-05-25 add in/out labels
2015-05-25 make case-size version of M2PA
2015-05-26 add tiny version for diecast case
2015-06-28 add m2rl r1
2015-06-28 update chibiOS checkout to latest 2.6 stable
2015-06-29 add pinout to bottom silk on m2r-r2
2015-06-29 try and model m2pa in box..
2015-06-29 add kicad proj for m2pa-m3mount
2015-06-29 add wiring diagram attempt
2015-07-22 add cheesy nosecone wiring diagram
2015-07-22 add potential m2r cover design
2015-07-22 add boms/zips for manufacture
2015-07-22 add svg render of docs/wiring.dia
2015-07-22 add dxf laser cut covers for m2fc/m2rl
2015-08-11 Started looking up what I will need to write the ADCs for M2
2015-08-12 new wiring diagram
2015-08-12 I have started on the drivers for the ADCs, but I got quite a few questions on how to proceed, please see quiestions in the comments in ADCs.c
2015-08-13 first go at hamming+interleaved ecc
2015-08-13 update ecc; works but isn't very good
2015-08-14 add ldpc generator
2015-08-14 rejig ldpc coder after much thought and experimentation
2015-08-14 working ldpc encoder/decoder. might need performance improvements.
2015-08-14 further work but no real improvements
2015-08-14 update docs
2015-08-17 update m2r board.h for r2
2015-08-19 almost ready to try it now. Adam: Could you have a look at it?
2015-08-20 fixed some error in the code: Still an error on initilising gptConGrp, but mainly OK
2015-08-20 m2r psk radio mode
2015-08-20 It compiledls!
2015-08-20 Added a thread
2015-08-21 add m2r shell over semihosting
2015-08-24 add first go at libldpcd in rust
2015-08-24 working libldpc
2015-08-25 update radio doc for psk
2015-08-25 add timing script
2015-08-26 lay out m2ground rust library
2015-08-27 add demonstration binary that saves to file
2015-08-27 annotate with comments
2015-08-28 allow tests to pass without my specific airspy
2015-08-31 use external airspy crate
2015-08-31 extra building stuff
2015-08-31 add old linker script to make building work or whatever
2015-08-31 add linker script to ADCs branch too
2015-09-01 some tweaks to ADC code. seems to mostly work now.
2015-09-02 Cleaned up some code
2015-09-03 Copied magno and gyro driver
2015-09-03 add downconverter and cic filter
2015-09-03 use assert_eq more
2015-09-03 add some tests and speed up the CIC
2015-09-03 It compilesgit add main.c Added Gyro and Magno to m2fc, TODO: Add tweeter and LED support, uncomment threads to start them
2015-09-04 add FIR filter and filter design
2015-09-04 improve CICs and integrate FIRs into DC
2015-09-04 clean up source
2015-09-04 add FIR test bin
2015-09-04 don't include main()s when testing
2015-09-05 update makefile and compare for new c libldpcd
2015-09-05 show file size states when make flashing
2015-09-05 work harder to not wake up the adxl thread while it's not sleeping
2015-09-05 update ms5611 driver to sleep better and do low temp tempco
2015-09-05 increase microSD buffer size to 4k items to help deal with sd wait states
2015-09-06 clean up main.c a little
2015-09-06 set the microsd log buffer a little smaller to avoid overfilling CCM
2015-09-06 rescue symbols from m2fc pcb
2015-09-06 uh.. update config.c to reflect reality
2015-09-06 add new C version of LDPC decoder (faster etc)
2015-09-06 refactor rust ldpcd a bit
2015-09-07 Added a mutex lock for the magno and gyro, no idea if it works
2015-09-07 Ready to test mutex lock
2015-09-07 Try MUTEX, hasn't been able to confirm it compiles
2015-09-07 Added a required library
2015-09-07 Added the MUTEX lock for baro and magno instead
2015-09-07 Fixed a bug in DMA conflict
2015-09-07 And another try
2015-09-07 And some more
2015-09-07 Added some more mutex locks
2015-09-08 Changed dma1_stream_1mutex to be an object instead of a pointer
2015-09-08 Did some changes to most of the code, added some global variables for the shell to read, might be a good idea to check if that creates some problems
2015-09-08 Added some shell commands, need help with pyro_fire
2015-09-09 ADCs now take the average of the thermo couples
2015-09-13 update analogue plotting script to show small chunks
2015-09-19 add m2telem
2015-09-19 Fix high pressure bug in state_estimation.c
2015-09-19 Brief update to README
2015-09-19 Tidy up after merging analogue and magno and gyro
2015-09-19 Import new datalogging and microSD from Badger 3
2015-09-19 Import config reading from B3
2015-09-19 put git version in config and log it
2015-09-19 let's stick with this mission.c, with slight update
2015-09-19 check in example config files
2015-09-19 add thread to run config_init in bigger stack
2015-09-19 fix typo in hmc5883l function name
2015-09-19 update shell commands a bit
2015-09-19 fix DMA allocations to minimise conflicts
2015-09-19 move mission states etc inside the implementation
2015-09-19 add own spi_select etc for ms5611 to work around mutex issue
2015-09-19 note that the pyro commands do block now
2015-09-19 run all the threads in main, just about.
2015-09-19 add config shell command
2015-09-19 have main alt be m AGL not m ASL
2015-09-19 Add some manufacturing files from laptop
2015-09-20 fix typo in state_estimation.c
2015-09-20 have magno and gyro be config-controllable
2015-09-20 early work on m2status
2015-09-22 m2status mostly done
2015-09-23 m2status again nearly done
2015-09-23 begin integrating new m2status/m2serial/m2telem
2015-09-23 first go at using m2status
2015-09-23 also use m2status for error reporting
2015-09-23 adxl using m2status yay
2015-09-23 more things using m2status
2015-09-24 set ublox to 10hz
2015-09-24 lower startup safety timer
2015-09-24 move m2rl code into its own folder
2015-09-25 m2status in shell and gyro
2015-09-25 m2status in microsd, mission, baro, pyro, se
2015-09-25 m2r gps work
2015-09-25 radio.c tweaks
2015-09-25 use m2status for radio strings
2015-09-25 beeper and LED link to m2status
2015-09-25 update beeper and led
2015-09-25 clean up all m2r warnings
2015-09-26 all getting close to flight ready
2015-09-27 final flight firmware
2015-10-11 m2telem_dump util
2015-10-16 early work in m2 avionics postmortem
2015-10-21 further work on m2 avionics postmortem. still early draft
2015-11-15 update postmortem some more
2016-05-13 simple ssb hab mode for m2r
2017-04-04 more mods to the m2r hab fw, inc pyro
